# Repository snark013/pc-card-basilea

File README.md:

# Basilea PC Card

[Русская версия](README_RU.md)

Main project repository: [git.snark13.com/snark13/basilea](https://git.snark13.com/snark13/basilea.git).

GitHub mirror: [github.com/snark013/pc-card-basilea](https://github.com/snark013/pc-card-basilea.git).

Basilea is an IBM PC-compatible processor board based on the M6117D system-on-chip, which integrates a 40 MHz 386SX processor and the M1217B chipset. The project is designed in KiCad.

Basilea is based on Evgeny Lozovoy’s [Kharon-386](https://github.com/UzixLS/pc-kharon-386) project.

## Project status

Version 1.2.2 has been assembled and tested. Release files are available in the repository.

A 32 MB RAM configuration using two 16 MB SIMMs has been tested. Mixed EDO and FPM operation has not been tested.

## Key features

- 40 MHz 386SX processor and M1217B chipset integrated into the M6117D.
- Two 72-pin SIMM slots supporting up to 32 MB of RAM.
- EDO and FPM memory support.
- PS/2 keyboard and mouse ports.
- Two serial COM ports available for external connections.
- CompactFlash (CF) card slot.
- Battery-backed real-time clock (RTC).
- PC speaker.

## RAM

The board provides two 72-pin SIMM slots and supports up to 32 MB of RAM. A configuration with two 16 MB modules has been tested.

- Single-sided modules are supported. Double-sided modules may be detected at less than their full capacity.
- Modules whose memory chips use different numbers of row and column address bits may also be detected at less than their full capacity.
- Both EDO and FPM modules are supported. Using two modules of different types together has not been tested and is not guaranteed to work.

## BIOS

The [roms/](roms/) directory contains separate AWARD and AMI BIOS images, as well as a combined image containing both versions. When using the combined image, SW1 selects the BIOS version.

**The AMI BIOS is recommended.**

## Serial ports

The serial controller provides four COM ports, all of which are detected by the system. Only two ports are routed on the PCB and available for external connections.

## Project files

- [basilea.kicad_pro](basilea.kicad_pro) — KiCad project.
- [basilea.kicad_sch](basilea.kicad_sch) — schematic.
- [basilea.kicad_pcb](basilea.kicad_pcb) — PCB layout.
- [basilea.pretty/](basilea.pretty/) and [Modules.pretty/](Modules.pretty/) — local footprint libraries.
- [docs/](docs/) — reference documentation.
- [roms/](roms/) — AWARD, AMI, and combined BIOS images.
- [release/](release/) — release files: Gerber files, PDF schematics, and interactive bills of materials.
- [images/1.2.2/](images/1.2.2/) — photos of the assembled version 1.2.2 board.

### Release files

| Version | Gerber files | Schematic | Interactive bill of materials |
| --- | --- | --- | --- |
| 1.2.2 | [ZIP](release/1.2.2/gerber.zip) | [PDF](release/1.2.2/basilea.pdf) | [HTML](release/1.2.2/ibom.html) |

## Revision history

### 1.2.2

- Optimized component placement.
- Changed all capacitors below 0.1 µF to the 0603 package size.
- Built the second working board version.

### 1.1

- Updated PCB silkscreen.

### 1.0

- Optimized component placement.

### 0.6

- Corrected CAS/RAS signal routing to the SIMM slots.

### 0.3

- Built the first board version.
- Identified incorrect CAS/RAS signal routing to the SIMM slots; corrected in version 0.6.

## Photos

Assembled version 1.2.2 board.

[Photos of the version 0.3 board](images/0.3/).

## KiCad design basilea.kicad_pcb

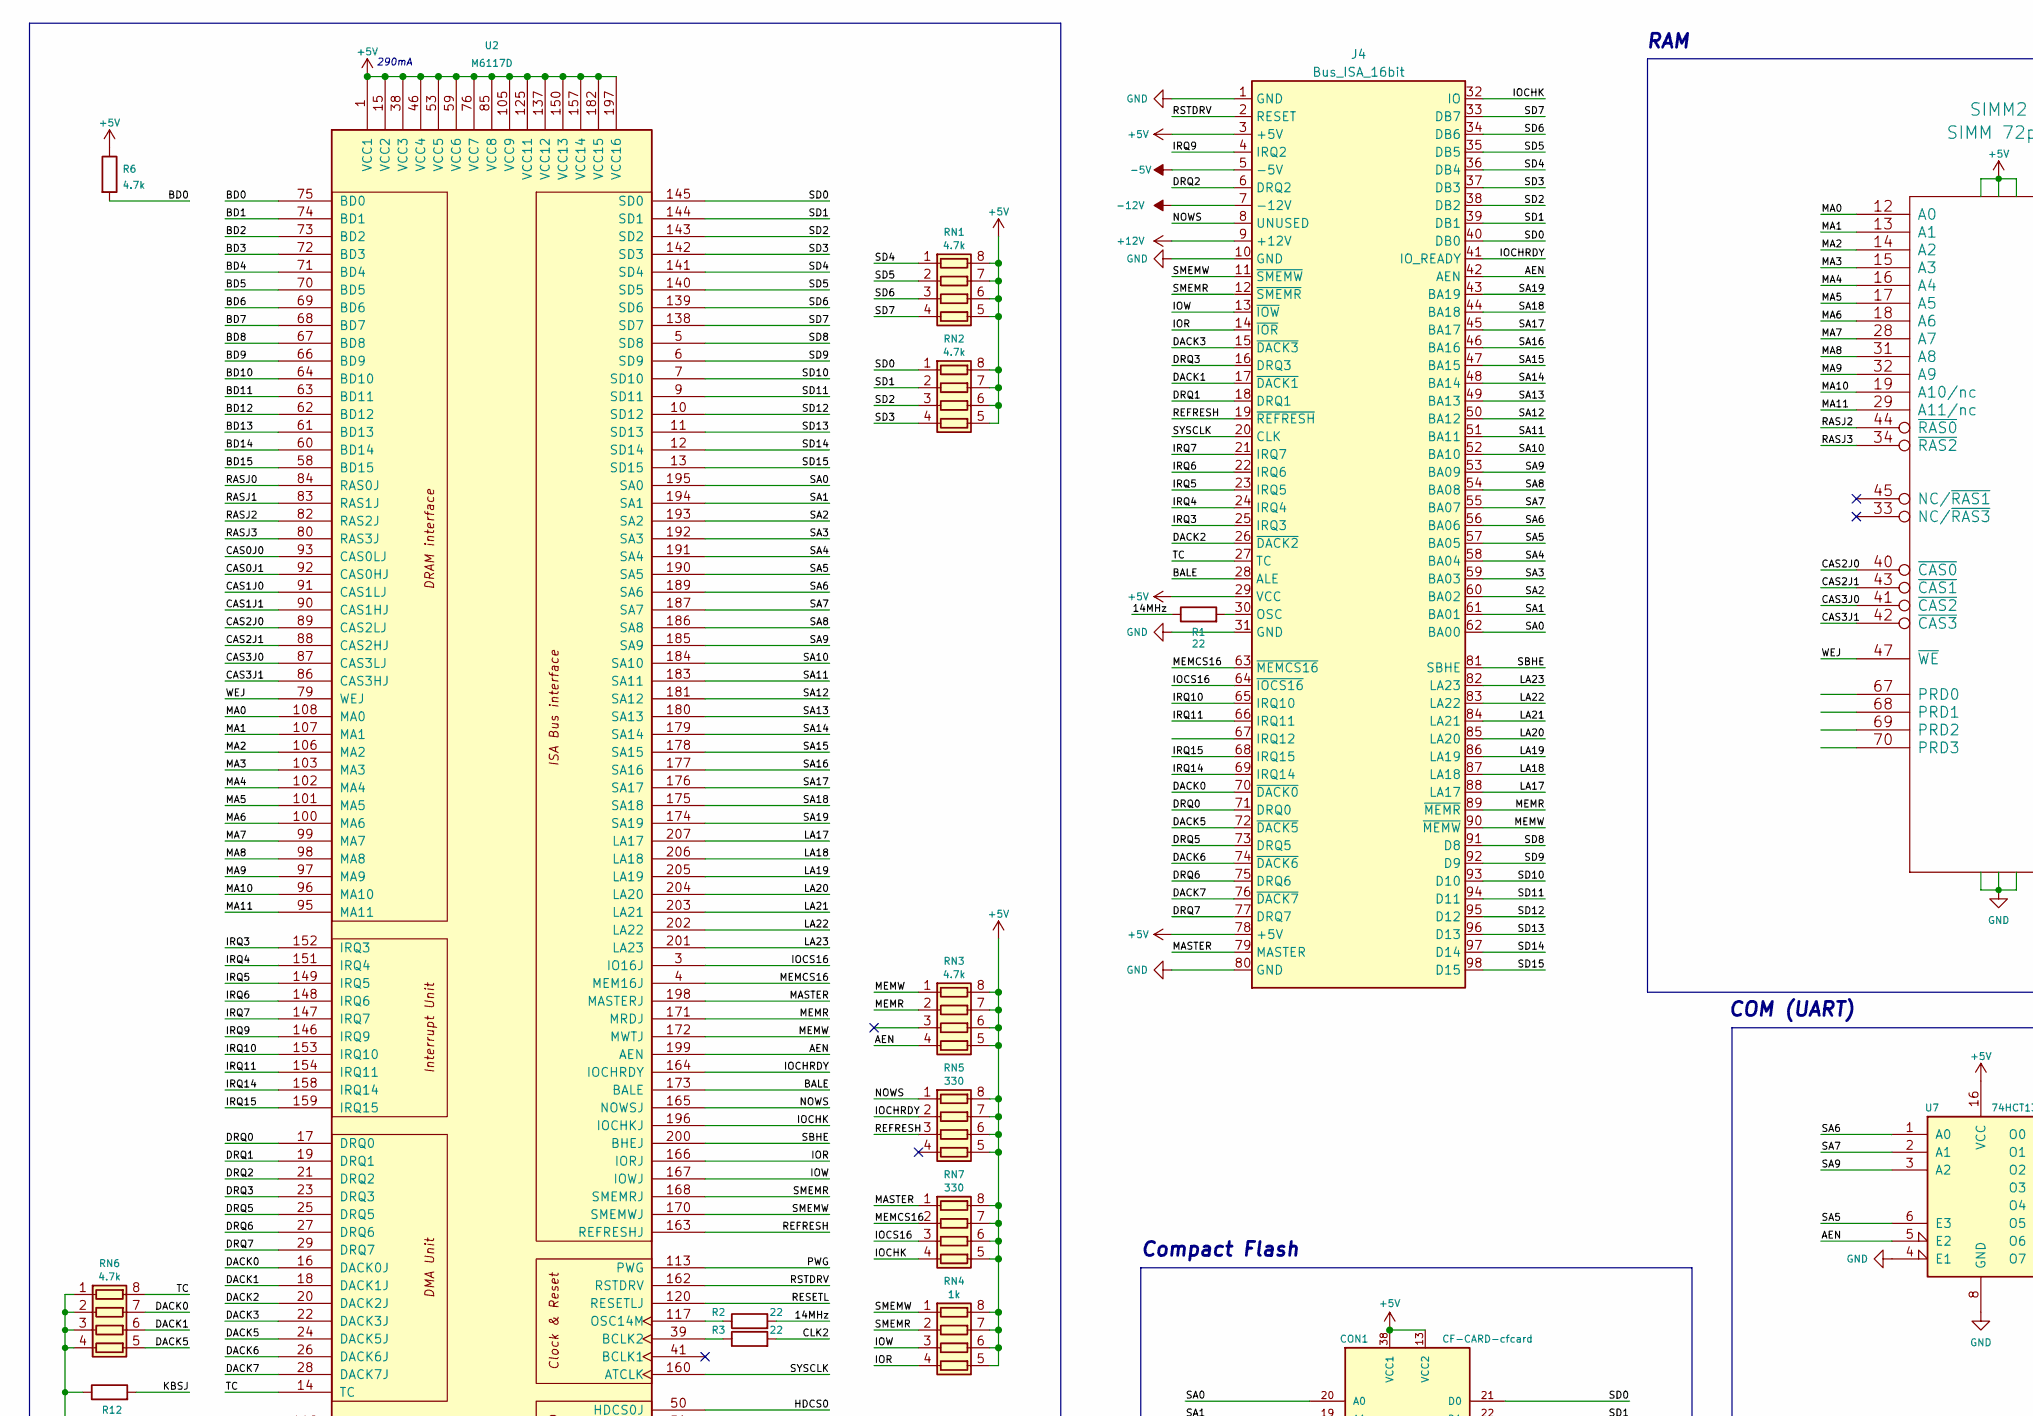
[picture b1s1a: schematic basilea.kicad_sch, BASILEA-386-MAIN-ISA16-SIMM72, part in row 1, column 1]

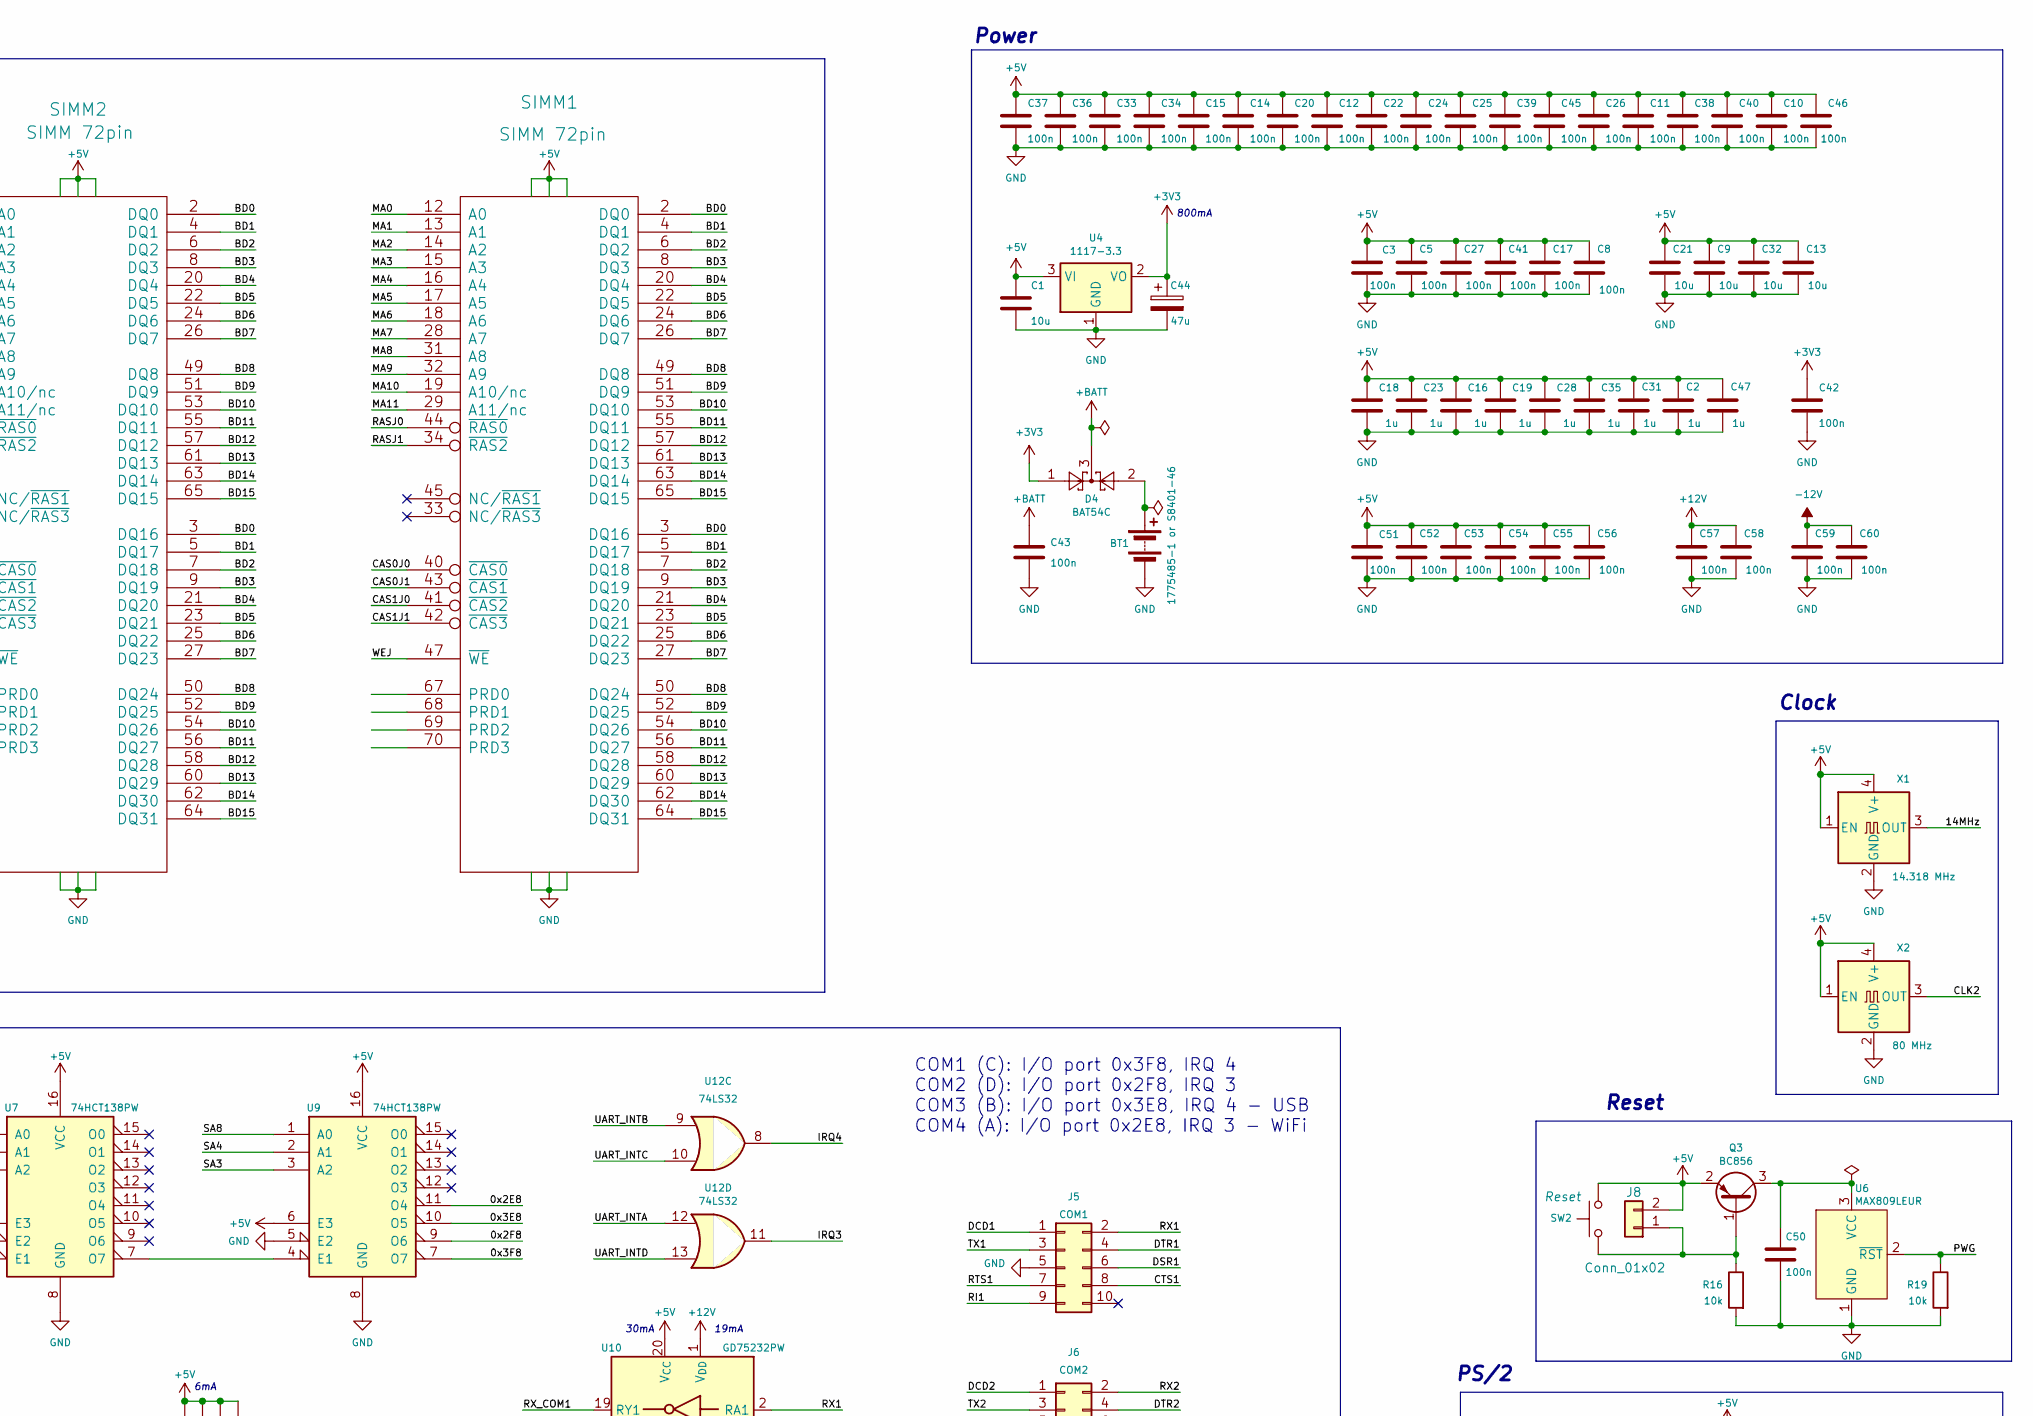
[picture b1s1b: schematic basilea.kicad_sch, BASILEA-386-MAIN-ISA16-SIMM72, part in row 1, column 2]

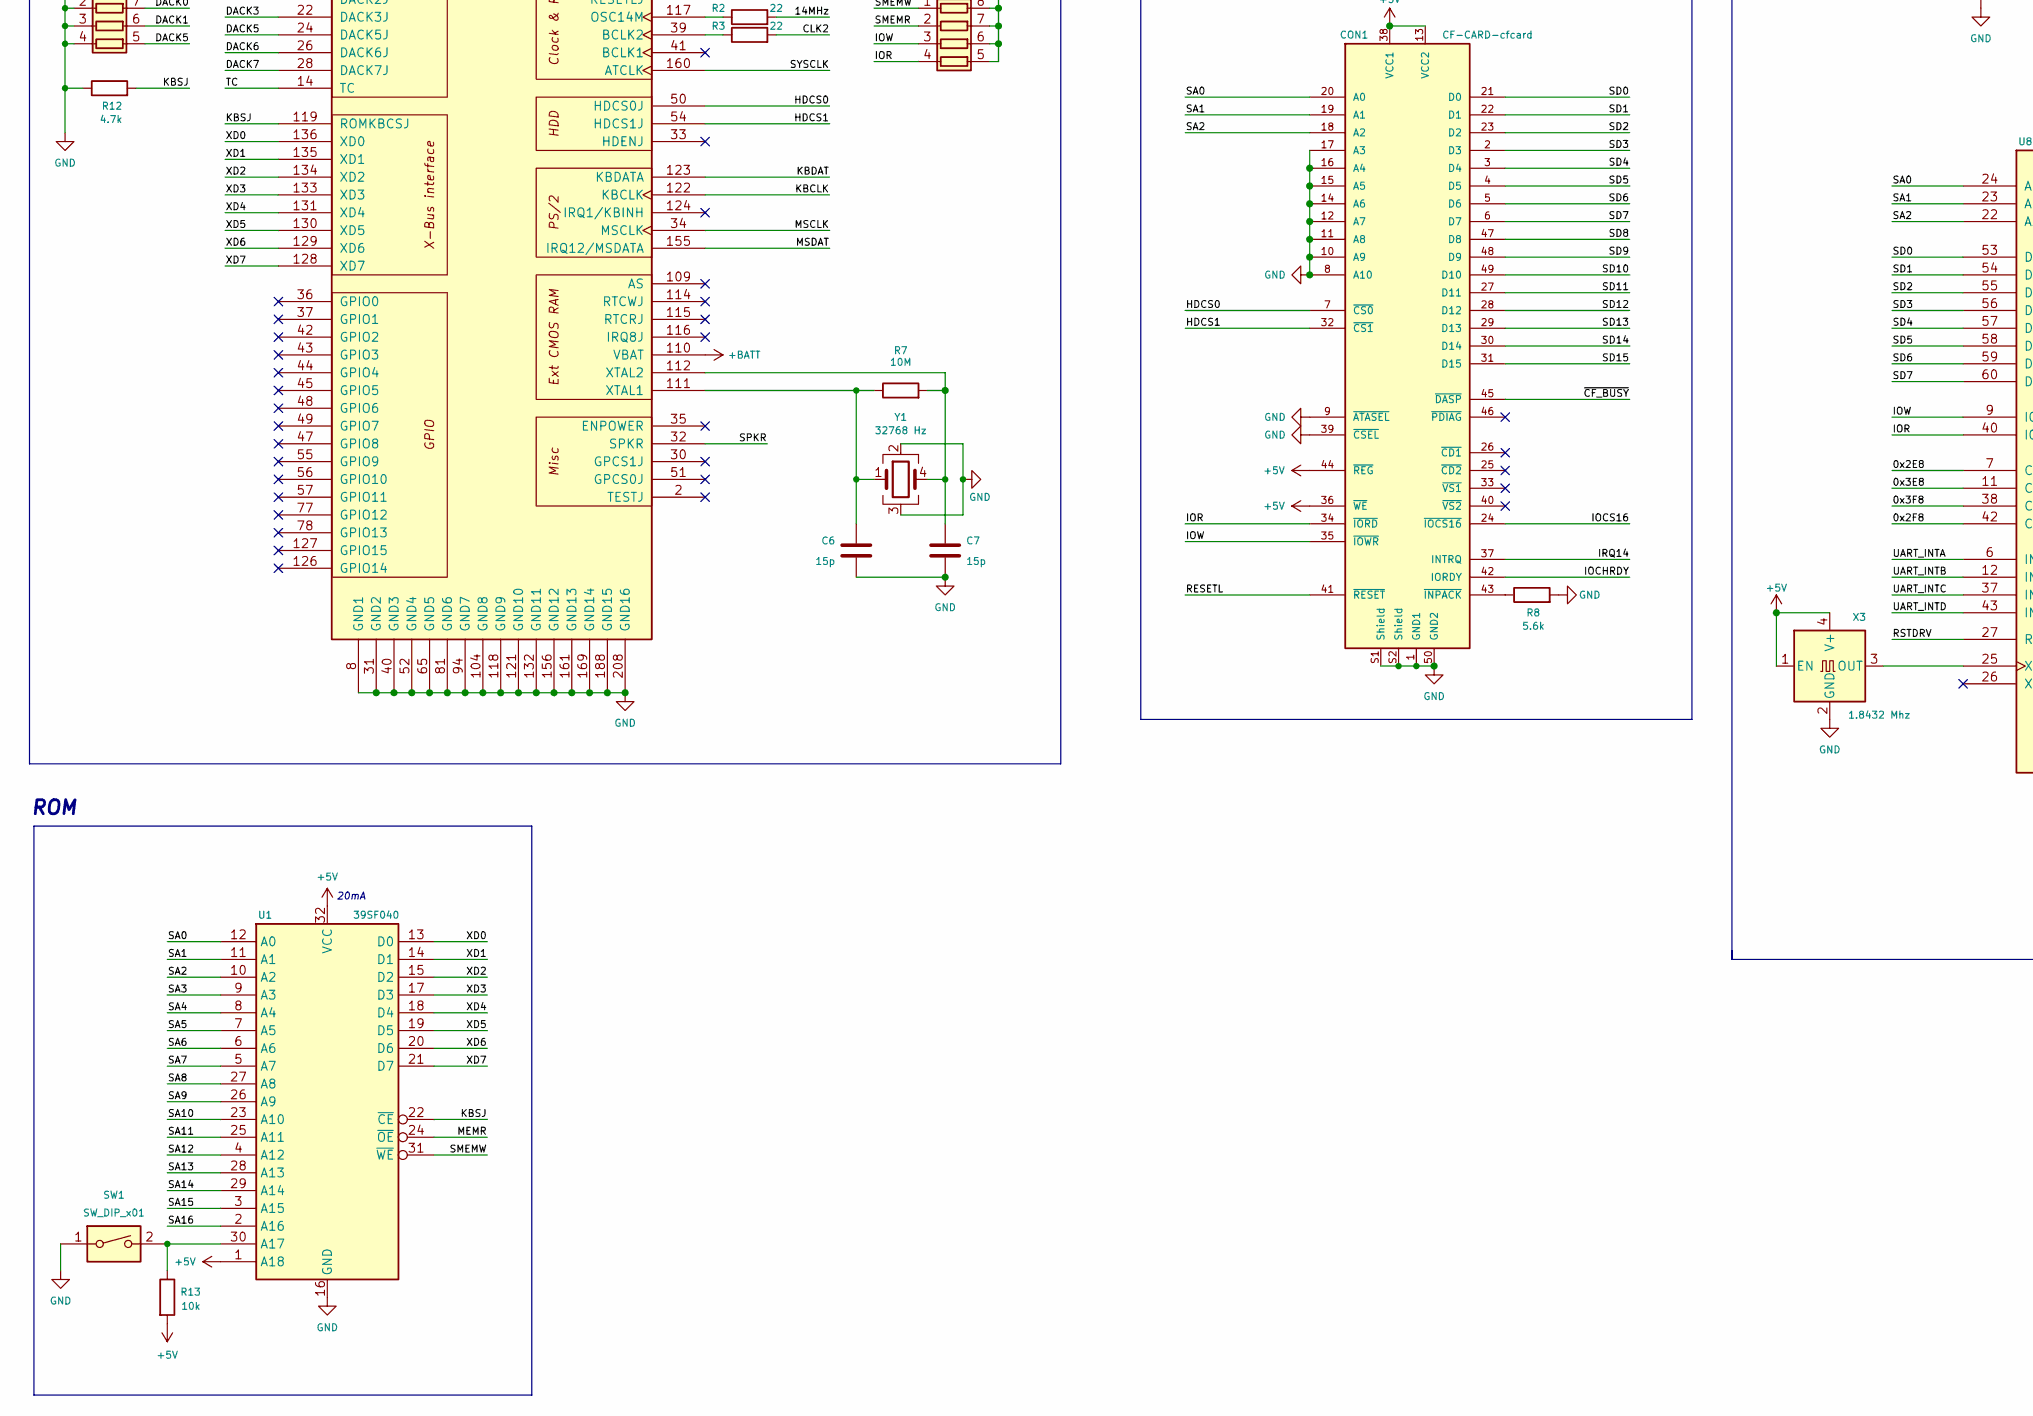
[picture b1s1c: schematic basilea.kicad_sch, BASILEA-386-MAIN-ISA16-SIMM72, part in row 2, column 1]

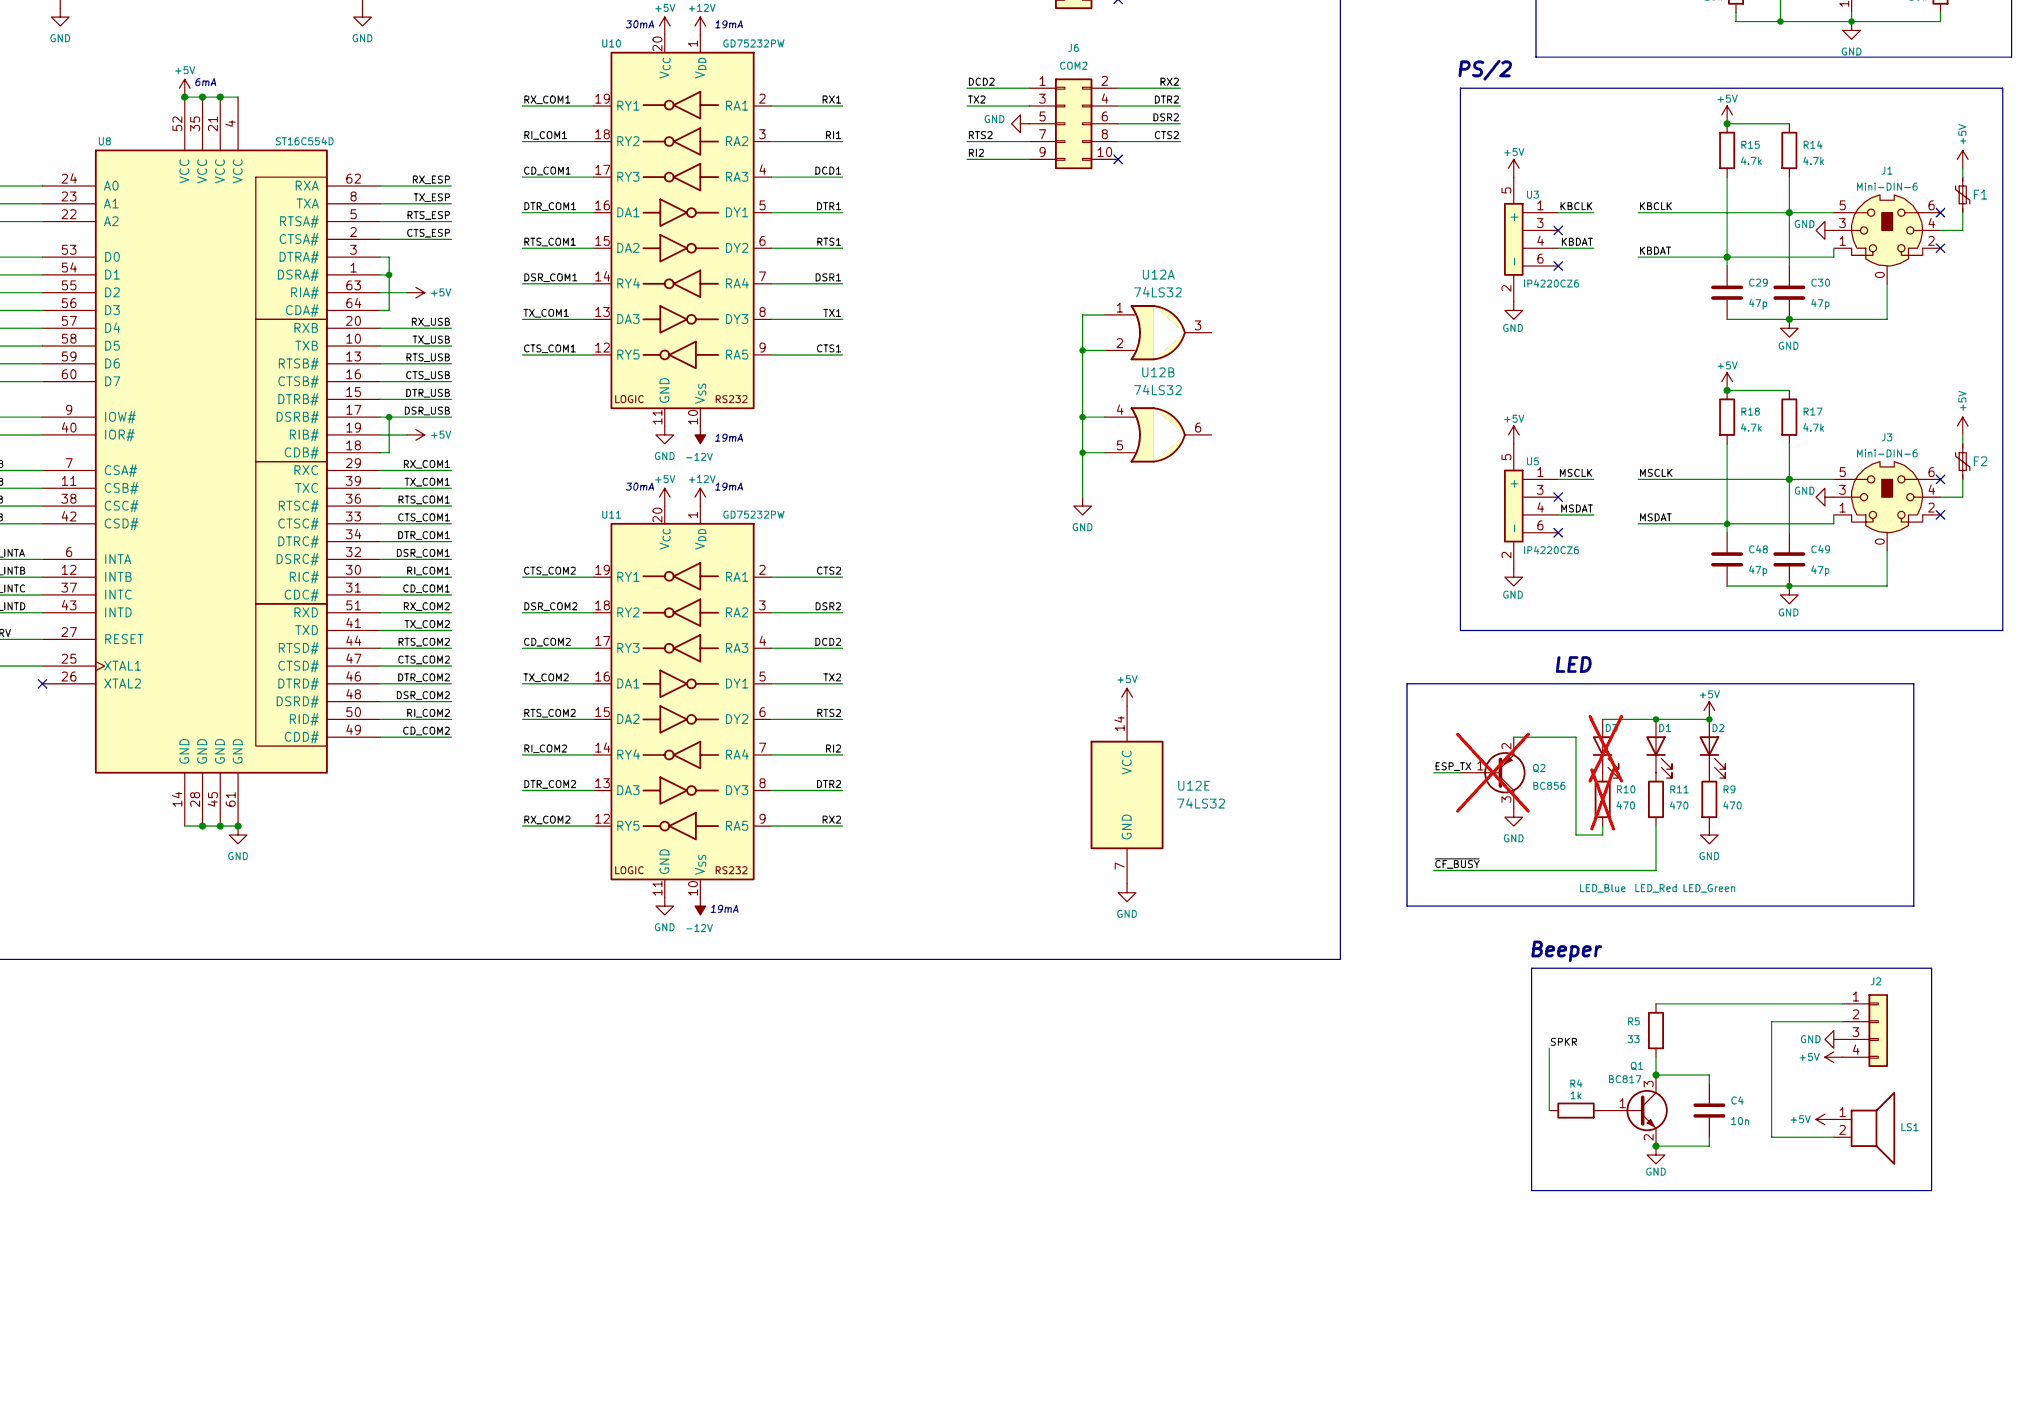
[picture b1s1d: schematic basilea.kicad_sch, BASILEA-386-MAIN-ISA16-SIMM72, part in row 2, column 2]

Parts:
BT1: 1775485-1 or S8401-46; Battery_Holder_Coin_2032_BS-7
C1, C9, C13, C21, C32: 10u; C_0805_2012Metric_Pad1.18x1.45mm_HandSolder
C2, C16, C18, C19, C23, C28, C31, C35, C47: 1u; C_0805_2012Metric_Pad1.18x1.45mm_HandSolder
C3, C5, C8, C10, C11, C12, C14, C15, C17, C20, C22, C24, C25, C26, C27, C33, C34, C36, C37, C38, C39, C40, C41, C42, C43, C45, C46, C50, C51, C52, C53, C54, C55, C56, C57, C58, C59, C60: 100n; C_0805_2012Metric_Pad1.18x1.45mm_HandSolder
C4: 10n; C_0603_1608Metric_Pad1.08x0.95mm_HandSolder
C6, C7: 15p; C_0603_1608Metric_Pad1.08x0.95mm_HandSolder
C29, C30, C48, C49: 47p; C_0603_1608Metric_Pad1.08x0.95mm_HandSolder
C44: 47u; CP_EIA-3528-21_Kemet-B_Pad1.50x2.35mm_HandSolder
CON1: CF-CARD-cfcard; TE_1734451-1-LONG
D1: LED_Red; LED_1206_3216Metric_Pad1.42x1.75mm_HandSolder
D2: LED_Green; LED_1206_3216Metric_Pad1.42x1.75mm_HandSolder
D3: LED_Blue; LED_1206_3216Metric_Pad1.42x1.75mm_HandSolder; not fitted
D4: BAT54C; SOT-23
F1, F2: Polyfuse_Small; Fuse_1206_3216Metric_Pad1.42x1.75mm_HandSolder
J1, J3: Mini-DIN-6; minidin-6
J2: Conn_01x04; PinHeader_1x04_P2.54mm_Vertical
J4: Bus_ISA_16bit; BUS_AT
J5: COM1; PinHeader_2x05_P2.54mm_Vertical
J6: COM2; PinHeader_2x05_P2.54mm_Vertical
J8: Conn_01x02; PinHeader_1x02_P2.54mm_Vertical
LS1: Speaker; Buzzer_12x9.5RM7.6
Q1: BC817; SOT-23
Q2: BC856; SOT-23; not fitted
Q3: BC856; SOT-23
R1, R2, R3: 22; R_0603_1608Metric_Pad0.98x0.95mm_HandSolder
R4: 1k; R_0603_1608Metric_Pad0.98x0.95mm_HandSolder
R5: 33; R_0805_2012Metric_Pad1.20x1.40mm_HandSolder
R6, R12, R14, R15, R17, R18: 4.7k; R_0603_1608Metric_Pad0.98x0.95mm_HandSolder
R7: 10M; R_0603_1608Metric_Pad0.98x0.95mm_HandSolder
R8: 5.6k; R_0603_1608Metric_Pad0.98x0.95mm_HandSolder
R9, R11: 470; R_0603_1608Metric_Pad0.98x0.95mm_HandSolder
R10: 470; R_0603_1608Metric_Pad0.98x0.95mm_HandSolder; not fitted
R13, R16, R19: 10k; R_0603_1608Metric_Pad0.98x0.95mm_HandSolder
RN1, RN2, RN3, RN6: 4.7k; R_Array_Convex_4x0603
RN4: 1k; R_Array_Convex_4x0603
RN5, RN7: 330; R_Array_Convex_4x0603
SIMM1, SIMM2: SIMM 72pin; DRAMM-SIMM72-2021
SW1: SW_DIP_x01; SW_DIP_SPSTx01_Slide_6.7x4.1mm_W7.62mm_P2.54mm_LowProfile
SW2: SW_Push; SW_Tactile_SPST_Angled_PTS645Vx83-2LFS
U1: 39SF040; PLCC-32_THT-Socket
U2: M6117D; PQFP-208_28x28mm_P0.5mm
U3, U5: IP4220CZ6; TSOP-6_1.65x3.05mm_P0.95mm
U4: 1117-3.3; SOT-223-3_TabPin2
U6: MAX809LEUR; SOT-23
U7, U9: 74HCT138PW; TSSOP-16_4.4x5mm_P0.65mm
U8: ST16C554D; LQFP-64_10x10mm_P0.5mm
U10, U11: GD75232PW; TSSOP-20_4.4x6.5mm_P0.65mm
U12: 74LS32; TSSOP-14_4.4x5mm_P0.65mm
X1: 14.318 MHz; Oscillator_SMD_7050_7.0x5.0mm
X2: 80 MHz; Oscillator_SMD_7050_7.0x5.0mm
X3: 1.8432 Mhz; Oscillator_SMD_EuroQuartz_XO91-4Pin_7.0x5.0mm
Y1: 32768 Hz; Crystal_SMD_SeikoEpson_MC306-4Pin_8.0x3.2mm_HandSoldering

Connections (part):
+3V3: C42.2, C44.1, D4.1, U4.2 (VO)
+5V: C1.2, C2.1, C3.2, C5.1, C8.1, C9.1, C10.2, C11.2, C12.2, C13.1, C14.2, C15.2, C16.2, C17.1, C18.2, C19.2, C20.2, C21.1, C22.2, C23.2, C24.2, C25.2, C26.2, C27.1, C28.2, C31.1, C32.1, C33.2, C34.2, C35.2, C36.2, C37.2, C38.2, C39.2, C40.2, C41.1, C45.2, C46.2, C47.1, C51.2, C52.1, C53.1, C54.1, C55.1, C56.1, CON1.13 (VCC2), CON1.36 (~WE), CON1.38 (VCC1), CON1.44 (~REG), D1.2 (A), D2.2 (A), D3.2 (A), F1.1, F2.1, J2.4, J4.3 (+5V), J4.29 (VCC), J4.78 (+5V), J8.2, LS1.1, Q3.2 (E), R6.1, R13.2, R14.1, R15.1, R17.1, R18.1, RN1.5 (R4.2), RN1.6 (R3.2), RN1.7 (R2.2), RN1.8 (R1.2), RN2.5 (R4.2), RN2.6 (R3.2), RN2.7 (R2.2), RN2.8 (R1.2), RN3.5 (R4.2), RN3.6 (R3.2), RN3.7 (R2.2), RN3.8 (R1.2), RN4.5 (R4.2)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
+12V: C57.1, C58.1, J4.9 (+12V), U10.1 (V_{DD}), U11.1 (V_{DD})
+BATT: C43.1, D4.3, U2.110 (VBAT)
-5V: J4.5 (-5V)
-12V: C59.1, C60.1, J4.7 (-12V), U10.10 (V_{SS}), U11.10 (V_{SS})
/0x2E8: U8.7 (CSA#), U9.11 (O4)
/0x2F8: U8.42 (CSD#), U9.9 (O6)
/0x3E8: U8.11 (CSB#), U9.10 (O5)
/0x3F8: U8.38 (CSC#), U9.7 (O7)
/14MHz: R1.1, R2.2, X1.3 (OUT)
/AEN: J4.42 (AEN), RN3.4 (R4.1), U2.199 (AEN), U7.5 (E2)
/BALE: J4.28 (ALE), U2.173 (BALE)
/BD0: R6.2, SIMM1.2 (DQ0), SIMM1.3 (DQ16), SIMM2.2 (DQ0), SIMM2.3 (DQ16), U2.75 (BD0)
/BD1: SIMM1.4 (DQ1), SIMM1.5 (DQ17), SIMM2.4 (DQ1), SIMM2.5 (DQ17), U2.74 (BD1)
/BD2: SIMM1.6 (DQ2), SIMM1.7 (DQ18), SIMM2.6 (DQ2), SIMM2.7 (DQ18), U2.73 (BD2)
/BD3: SIMM1.8 (DQ3), SIMM1.9 (DQ19), SIMM2.8 (DQ3), SIMM2.9 (DQ19), U2.72 (BD3)
/BD4: SIMM1.20 (DQ4), SIMM1.21 (DQ20), SIMM2.20 (DQ4), SIMM2.21 (DQ20), U2.71 (BD4)
/BD5: SIMM1.22 (DQ5), SIMM1.23 (DQ21), SIMM2.22 (DQ5), SIMM2.23 (DQ21), U2.70 (BD5)
/BD6: SIMM1.24 (DQ6), SIMM1.25 (DQ22), SIMM2.24 (DQ6), SIMM2.25 (DQ22), U2.69 (BD6)
/BD7: SIMM1.26 (DQ7), SIMM1.27 (DQ23), SIMM2.26 (DQ7), SIMM2.27 (DQ23), U2.68 (BD7)
/BD8: SIMM1.49 (DQ8), SIMM1.50 (DQ24), SIMM2.49 (DQ8), SIMM2.50 (DQ24), U2.67 (BD8)
/BD9: SIMM1.51 (DQ9), SIMM1.52 (DQ25), SIMM2.51 (DQ9), SIMM2.52 (DQ25), U2.66 (BD9)
/BD10: SIMM1.53 (DQ10), SIMM1.54 (DQ26), SIMM2.53 (DQ10), SIMM2.54 (DQ26), U2.64 (BD10)
/BD11: SIMM1.55 (DQ11), SIMM1.56 (DQ27), SIMM2.55 (DQ11), SIMM2.56 (DQ27), U2.63 (BD11)
/BD12: SIMM1.57 (DQ12), SIMM1.58 (DQ28), SIMM2.57 (DQ12), SIMM2.58 (DQ28), U2.62 (BD12)
/BD13: SIMM1.60 (DQ29), SIMM1.61 (DQ13), SIMM2.60 (DQ29), SIMM2.61 (DQ13), U2.61 (BD13)
/BD14: SIMM1.62 (DQ30), SIMM1.63 (DQ14), SIMM2.62 (DQ30), SIMM2.63 (DQ14), U2.60 (BD14)
/BD15: SIMM1.64 (DQ31), SIMM1.65 (DQ15), SIMM2.64 (DQ31), SIMM2.65 (DQ15), U2.58 (BD15)
/CAS0J0: SIMM1.40 (~CAS0), U2.93 (CAS0LJ)
/CAS0J1: SIMM1.43 (~CAS1), U2.92 (CAS0HJ)
/CAS1J0: SIMM1.41 (~CAS2), U2.91 (CAS1LJ)
/CAS1J1: SIMM1.42 (~CAS3), U2.90 (CAS1HJ)
/CAS2J0: SIMM2.40 (~CAS0), U2.89 (CAS2LJ)
/CAS2J1: SIMM2.43 (~CAS1), U2.88 (CAS2HJ)
/CAS3J0: SIMM2.41 (~CAS2), U2.87 (CAS3LJ)
/CAS3J1: SIMM2.42 (~CAS3), U2.86 (CAS3HJ)
/CD_COM1: U8.31 (CDC#), U10.17 (RY3)
/CD_COM2: U8.49 (CDD#), U11.17 (RY3)
/CLK2: R3.2, X2.3 (OUT)
/CTS1: J5.8, U10.9 (RA5)
/CTS2: J6.8, U11.2 (RA1)
/CTS_COM1: U8.33 (CTSC#), U10.12 (RY5)
/CTS_COM2: U8.47 (CTSD#), U11.19 (RY1)
/CTS_ESP: U8.2 (CTSA#)
/CTS_USB: U8.16 (CTSB#)
/DACK0: J4.70 (~DACK0), RN6.7 (R2.2), U2.16 (DACK0J)
/DACK1: J4.17 (~DACK1), RN6.6 (R3.2), U2.18 (DACK1J)
/DACK2: J4.26 (~DACK2), U2.20 (DACK2J)
/DACK3: J4.15 (~DACK3), U2.22 (DACK3J)
/DACK5: J4.72 (~DACK5), RN6.5 (R4.2), U2.24 (DACK5J)
/DACK6: J4.74 (~DACK6), U2.26 (DACK6J)
/DACK7: J4.76 (~DACK7), U2.28 (DACK7J)
/DCD1: J5.1, U10.4 (RA3)
/DCD2: J6.1, U11.4 (RA3)
/DRQ0: J4.71 (DRQ0), U2.17 (DRQ0)
/DRQ1: J4.18 (DRQ1), U2.19 (DRQ1)
/DRQ2: J4.6 (DRQ2), U2.21 (DRQ2)
/DRQ3: J4.16 (DRQ3), U2.23 (DRQ3)
/DRQ5: J4.73 (DRQ5), U2.25 (DRQ5)
/DRQ6: J4.75 (DRQ6), U2.27 (DRQ6)
/DRQ7: J4.77 (DRQ7), U2.29 (DRQ7)
/DSR1: J5.6, U10.7 (RA4)
/DSR2: J6.6, U11.3 (RA2)
/DSR_COM1: U8.32 (DSRC#), U10.14 (RY4)
/DSR_COM2: U8.48 (DSRD#), U11.18 (RY2)
/DSR_USB: U8.17 (DSRB#), U8.18 (CDB#)
/DTR1: J5.4, U10.5 (DY1)
/DTR2: J6.4, U11.8 (DY3)
/DTR_COM1: U8.34 (DTRC#), U10.16 (DA1)
/DTR_COM2: U8.46 (DTRD#), U11.13 (DA3)
/DTR_USB: U8.15 (DTRB#)
/HDCS0: CON1.7 (~CS0), U2.50 (HDCS0J)
/HDCS1: CON1.32 (~CS1), U2.54 (HDCS1J)
/IOCHK: J4.32 (IO), RN7.4 (R4.1), U2.196 (IOCHKJ)
/IOCHRDY: CON1.42 (IORDY), J4.41 (IO_READY), RN5.2 (R2.1), U2.164 (IOCHRDY)
/IOCS16: CON1.24 (~IOCS16), J4.64 (~IOCS16), RN7.3 (R3.1), U2.3 (IO16J)
/IOR: CON1.34 (~IORD), J4.14 (~IOR), RN4.4 (R4.1), U2.166 (IORJ), U8.40 (IOR#)
/IOW: CON1.35 (~IOWR), J4.13 (~IOW), RN4.3 (R3.1), U2.167 (IOWJ), U8.9 (IOW#)
/IRQ3: J4.25 (IRQ3), U2.152 (IRQ3), U12.11
/IRQ4: J4.24 (IRQ4), U2.151 (IRQ4), U12.8
/IRQ5: J4.23 (IRQ5), U2.149 (IRQ5)
/IRQ6: J4.22 (IRQ6), U2.148 (IRQ6)
/IRQ7: J4.21 (IRQ7), U2.147 (IRQ7)
/IRQ9: J4.4 (IRQ2), U2.146 (IRQ9)
/IRQ10: J4.65 (IRQ10), U2.153 (IRQ10)
/IRQ11: J4.66 (IRQ11), U2.154 (IRQ11)
/IRQ14: CON1.37 (INTRQ), J4.69 (IRQ14), U2.158 (IRQ14)
/IRQ15: J4.68 (IRQ15), U2.159 (IRQ15)
/KBCLK: C30.1, J1.5, R14.2, U2.122 (KBCLK), U3.1
/KBDAT: C29.1, J1.1, R15.2, U2.123 (KBDATA), U3.4
/KBSJ: R12.2, U1.22 (~CE), U2.119 (ROMKBCSJ)
/LA17: J4.88 (LA17), U2.207 (LA17)
/LA18: J4.87 (LA18), U2.206 (LA18)
/LA19: J4.86 (LA19), U2.205 (LA19)
/LA20: J4.85 (LA20), U2.204 (LA20)
/LA21: J4.84 (LA21), U2.203 (LA21)
/LA22: J4.83 (LA22), U2.202 (LA22)
/LA23: J4.82 (LA23), U2.201 (LA23)
/MA0: SIMM1.12 (A0), SIMM2.12 (A0), U2.108 (MA0)
/MA1: SIMM1.13 (A1), SIMM2.13 (A1), U2.107 (MA1)
/MA2: SIMM1.14 (A2), SIMM2.14 (A2), U2.106 (MA2)
/MA3: SIMM1.15 (A3), SIMM2.15 (A3), U2.103 (MA3)
/MA4: SIMM1.16 (A4), SIMM2.16 (A4), U2.102 (MA4)
/MA5: SIMM1.17 (A5), SIMM2.17 (A5), U2.101 (MA5)
/MA6: SIMM1.18 (A6), SIMM2.18 (A6), U2.100 (MA6)
/MA7: SIMM1.28 (A7), SIMM2.28 (A7), U2.99 (MA7)
/MA8: SIMM1.31 (A8), SIMM2.31 (A8), U2.98 (MA8)
/MA9: SIMM1.32 (A9), SIMM2.32 (A9), U2.97 (MA9)
/MA10: SIMM1.19 (A10/nc), SIMM2.19 (A10/nc), U2.96 (MA10)
/MA11: SIMM1.29 (A11/nc), SIMM2.29 (A11/nc), U2.95 (MA11)
/MASTER: J4.79 (MASTER), RN7.1 (R1.1), U2.198 (MASTERJ)
/MEMCS16: J4.63 (~MEMCS16), RN7.2 (R2.1), U2.4 (MEM16J)
/MEMR: J4.89 (~MEMR), RN3.2 (R2.1), U1.24 (~OE), U2.171 (MRDJ)
/MEMW: J4.90 (~MEMW), RN3.1 (R1.1), U2.172 (MWTJ)
/MSCLK: C49.1, J3.5, R17.2, U2.34 (MSCLK), U5.1
/MSDAT: C48.1, J3.1, R18.2, U2.155 (IRQ12/MSDATA), U5.4
/NOWS: J4.8 (UNUSED), RN5.1 (R1.1), U2.165 (NOWSJ)
/PWG: R19.1, U2.113 (PWG), U6.2 (~RST)
/RASJ0: SIMM1.44 (~RAS0), U2.84 (RAS0J)
/RASJ1: SIMM1.34 (~RAS2), U2.83 (RAS1J)
/RASJ2: SIMM2.44 (~RAS0), U2.82 (RAS2J)
/RASJ3: SIMM2.34 (~RAS2), U2.80 (RAS3J)
/REFRESH: J4.19 (~REFRESH), RN5.3 (R3.1), U2.163 (REFRESHJ)
/RESETL: CON1.41 (~RESET), U2.120 (RESETLJ)
/RI1: J5.9, U10.3 (RA2)
/RI2: J6.9, U11.7 (RA4)
/RI_COM1: U8.30 (RIC#), U10.18 (RY2)
/RI_COM2: U8.50 (RID#), U11.14 (RY4)
/RSTDRV: J4.2 (RESET), U2.162 (RSTDRV), U8.27 (RESET)
/RTS1: J5.7, U10.6 (DY2)
/RTS2: J6.7, U11.6 (DY2)
/RTS_COM1: U8.36 (RTSC#), U10.15 (DA2)
/RTS_COM2: U8.44 (RTSD#), U11.15 (DA2)
/RTS_ESP: U8.5 (RTSA#)
/RTS_USB: U8.13 (RTSB#)
/RX1: J5.2, U10.2 (RA1)
/RX2: J6.2, U11.9 (RA5)
/RX_COM1: U8.29 (RXC), U10.19 (RY1)
/RX_COM2: U8.51 (RXD), U11.12 (RY5)
/RX_ESP: U8.62 (RXA)
/RX_USB: U8.20 (RXB)
/SA0: CON1.20 (A0), J4.62 (BA00), U1.12 (A0), U2.195 (SA0), U8.24 (A0)
/SA1: CON1.19 (A1), J4.61 (BA01), U1.11 (A1), U2.194 (SA1), U8.23 (A1)
/SA2: CON1.18 (A2), J4.60 (BA02), U1.10 (A2), U2.193 (SA2), U8.22 (A2)
/SA3: J4.59 (BA03), U1.9 (A3), U2.192 (SA3), U9.3 (A2)
/SA4: J4.58 (BA04), U1.8 (A4), U2.191 (SA4), U9.2 (A1)
/SA5: J4.57 (BA05), U1.7 (A5), U2.190 (SA5), U7.6 (E3)
/SA6: J4.56 (BA06), U1.6 (A6), U2.189 (SA6), U7.1 (A0)
/SA7: J4.55 (BA07), U1.5 (A7), U2.187 (SA7), U7.2 (A1)
/SA8: J4.54 (BA08), U1.27 (A8), U2.186 (SA8), U9.1 (A0)
/SA9: J4.53 (BA09), U1.26 (A9), U2.185 (SA9), U7.3 (A2)
/SA10: J4.52 (BA10), U1.23 (A10), U2.184 (SA10)
/SA11: J4.51 (BA11), U1.25 (A11), U2.183 (SA11)
/SA12: J4.50 (BA12), U1.4 (A12), U2.181 (SA12)
/SA13: J4.49 (BA13), U1.28 (A13), U2.180 (SA13)
/SA14: J4.48 (BA14), U1.29 (A14), U2.179 (SA14)
/SA15: J4.47 (BA15), U1.3 (A15), U2.178 (SA15)
/SA16: J4.46 (BA16), U1.2 (A16), U2.177 (SA16)
/SA17: J4.45 (BA17), U2.176 (SA17)
/SA18: J4.44 (BA18), U2.175 (SA18)
/SA19: J4.43 (BA19), U2.174 (SA19)
/SBHE: J4.81 (SBHE), U2.200 (BHEJ)
/SD0: CON1.21 (D0), J4.40 (DB0), RN2.1 (R1.1), U2.145 (SD0), U8.53 (D0)
/SD1: CON1.22 (D1), J4.39 (DB1), RN2.2 (R2.1), U2.144 (SD1), U8.54 (D1)
/SD2: CON1.23 (D2), J4.38 (DB2), RN2.3 (R3.1), U2.143 (SD2), U8.55 (D2)
/SD3: CON1.2 (D3), J4.37 (DB3), RN2.4 (R4.1), U2.142 (SD3), U8.56 (D3)
/SD4: CON1.3 (D4), J4.36 (DB4), RN1.1 (R1.1), U2.141 (SD4), U8.57 (D4)
/SD5: CON1.4 (D5), J4.35 (DB5), RN1.2 (R2.1), U2.140 (SD5), U8.58 (D5)
/SD6: CON1.5 (D6), J4.34 (DB6), RN1.3 (R3.1), U2.139 (SD6), U8.59 (D6)
/SD7: CON1.6 (D7), J4.33 (DB7), RN1.4 (R4.1), U2.138 (SD7), U8.60 (D7)
/SD8: CON1.47 (D8), J4.91 (D8), U2.5 (SD8)
/SD9: CON1.48 (D9), J4.92 (D9), U2.6 (SD9)
/SD10: CON1.49 (D10), J4.93 (D10), U2.7 (SD10)
/SD11: CON1.27 (D11), J4.94 (D11), U2.9 (SD11)
/SD12: CON1.28 (D12), J4.95 (D12), U2.10 (SD12)
/SD13: CON1.29 (D13), J4.96 (D13), U2.11 (SD13)
/SD14: CON1.30 (D14), J4.97 (D14), U2.12 (SD14)
/SD15: CON1.31 (D15), J4.98 (D15), U2.13 (SD15)
/SMEMR: J4.12 (~SMEMR), RN4.2 (R2.1), U2.168 (SMEMRJ)
/SMEMW: J4.11 (~SMEMW), RN4.1 (R1.1), U1.31 (~WE), U2.170 (SMEMWJ)
/SPKR: R4.1, U2.32 (SPKR)
/SYSCLK: J4.20 (CLK), U2.160 (ATCLK)
/TC: J4.27 (TC), RN6.8 (R1.2), U2.14 (TC)
/TX1: J5.3, U10.8 (DY3)
/TX2: J6.3, U11.5 (DY1)
/TX_COM1: U8.39 (TXC), U10.13 (DA3)
/TX_COM2: U8.41 (TXD), U11.16 (DA1)
/TX_ESP: U8.8 (TXA)
/TX_USB: U8.10 (TXB)
/UART_INTA: U8.6 (INTA), U12.12
/UART_INTB: U8.12 (INTB), U12.9
/UART_INTC: U8.37 (INTC), U12.10
/UART_INTD: U8.43 (INTD), U12.13
/WEJ: SIMM1.47 (~WE), SIMM2.47 (~WE), U2.79 (WEJ)
/XD0: U1.13 (D0), U2.136 (XD0)
/XD1: U1.14 (D1), U2.135 (XD1)
/XD2: U1.15 (D2), U2.134 (XD2)
/XD3: U1.17 (D3), U2.133 (XD3)
/XD4: U1.18 (D4), U2.131 (XD4)
/XD5: U1.19 (D5), U2.130 (XD5)
/XD6: U1.20 (D6), U2.129 (XD6)
/XD7: U1.21 (D7), U2.128 (XD7)
/~CF_BUSY: CON1.45 (~DASP), R11.2
GND: BT1.2 (-), C1.1, C2.2, C3.1, C4.2, C5.2, C6.2, C7.2, C8.2, C9.2, C10.1, C11.1, C12.1, C13.2, C14.1, C15.1, C16.1, C17.2, C18.1, C19.1, C20.1, C21.2, C22.1, C23.1, C24.1, C25.1, C26.1, C27.2, C28.1, C29.2, C30.2, C31.2, C32.2, C33.1, C34.1, C35.1, C36.1, C37.1, C38.1, C39.1, C40.1, C41.2, C42.1, C43.2, C44.2, C45.1, C46.1, C47.2, C48.2, C49.2, C50.2, C51.1, C52.2, C53.2, C54.2, C55.2, C56.2, C57.2, C58.2, C59.2, C60.2, CON1.1 (GND1), CON1.8 (A10), CON1.9 (~ATASEL), CON1.10 (A9), CON1.11 (A8), CON1.12 (A7), CON1.14 (A6), CON1.15 (A5), CON1.16 (A4), CON1.17 (A3), CON1.39 (~CSEL), CON1.50 (GND2), CON1.S1 (Shield), CON1.S2 (Shield), J1.0, J1.3, J2.3, J3.0, J3.3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
unnamed: BT1.1 (+), D4.2
unnamed: CON1.43 (~INPACK), R8.1
unnamed: D1.1 (K), R11.1
unnamed: D2.1 (K), R9.1
unnamed: D3.1 (K), R10.1
unnamed: F1.2, J1.4
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
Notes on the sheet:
800mA
19mA
Beeper
290mA
Reset
30mA
20mA
Power
COM1 (C): I/O port 0x3F8, IRQ 4 COM2 (D): I/O port 0x2F8, IRQ 3 COM3 (B): I/O port 0x3E8, IRQ 4 - USB COM4 (A): I/O port 0x2E8, IRQ 3 - WiFi
LED
RAM
6mA
Clock
ROM
COM (UART)
PS/2
Compact Flash

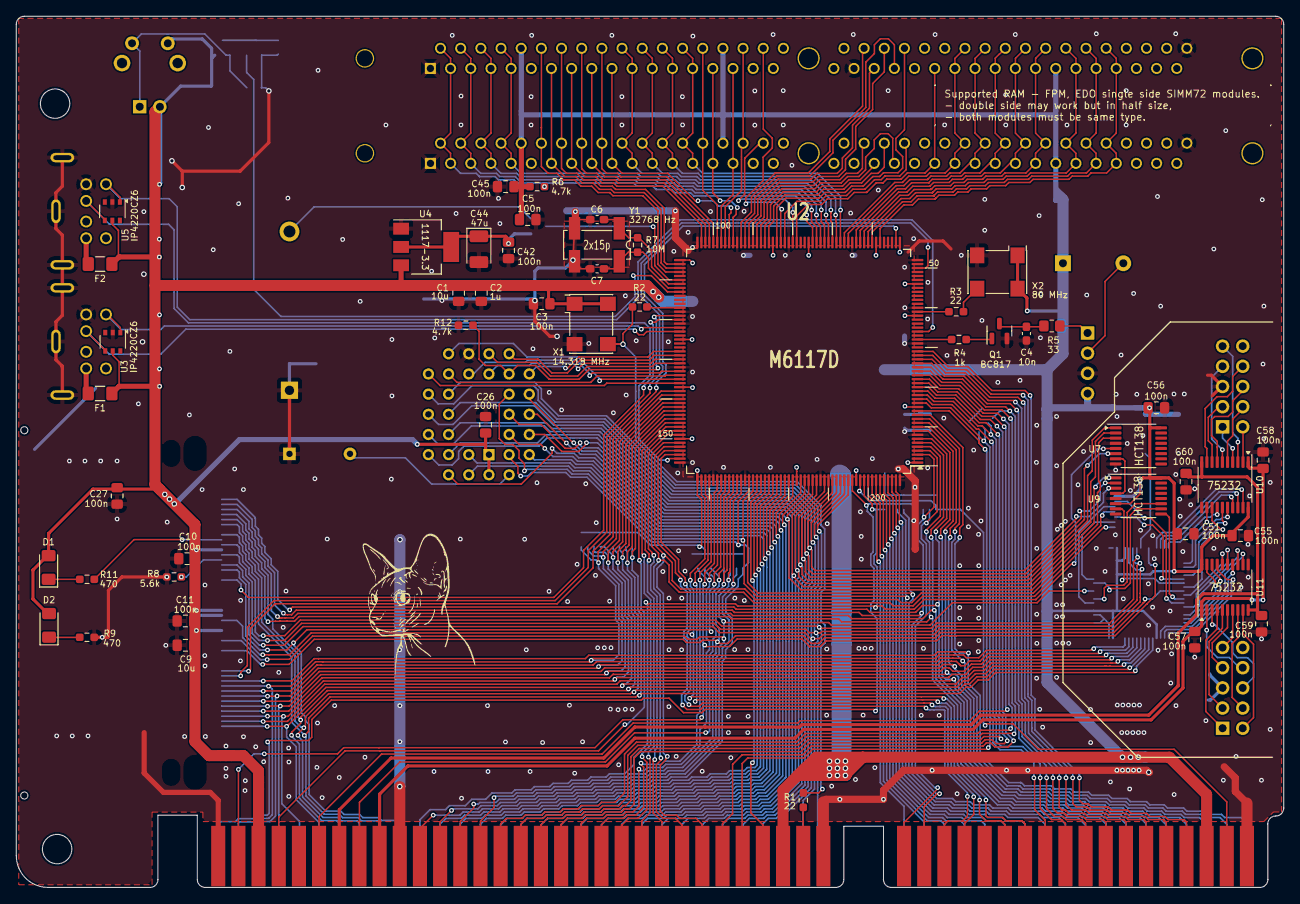
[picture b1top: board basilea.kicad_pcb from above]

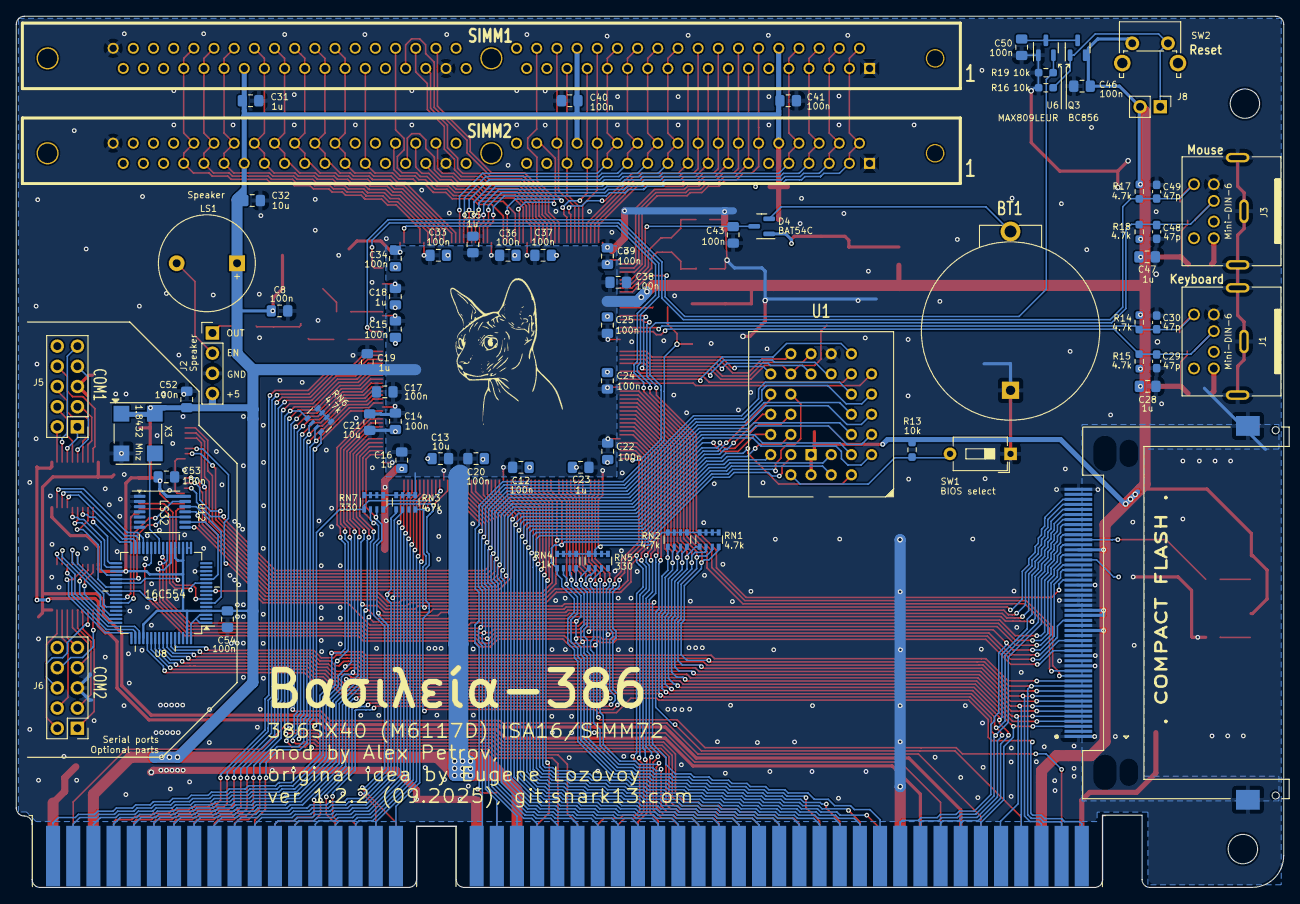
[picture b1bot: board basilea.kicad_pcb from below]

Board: 2 copper layers, 159.6 x 109.7 mm, 122 parts (73 on the bottom side), 216 nets.
